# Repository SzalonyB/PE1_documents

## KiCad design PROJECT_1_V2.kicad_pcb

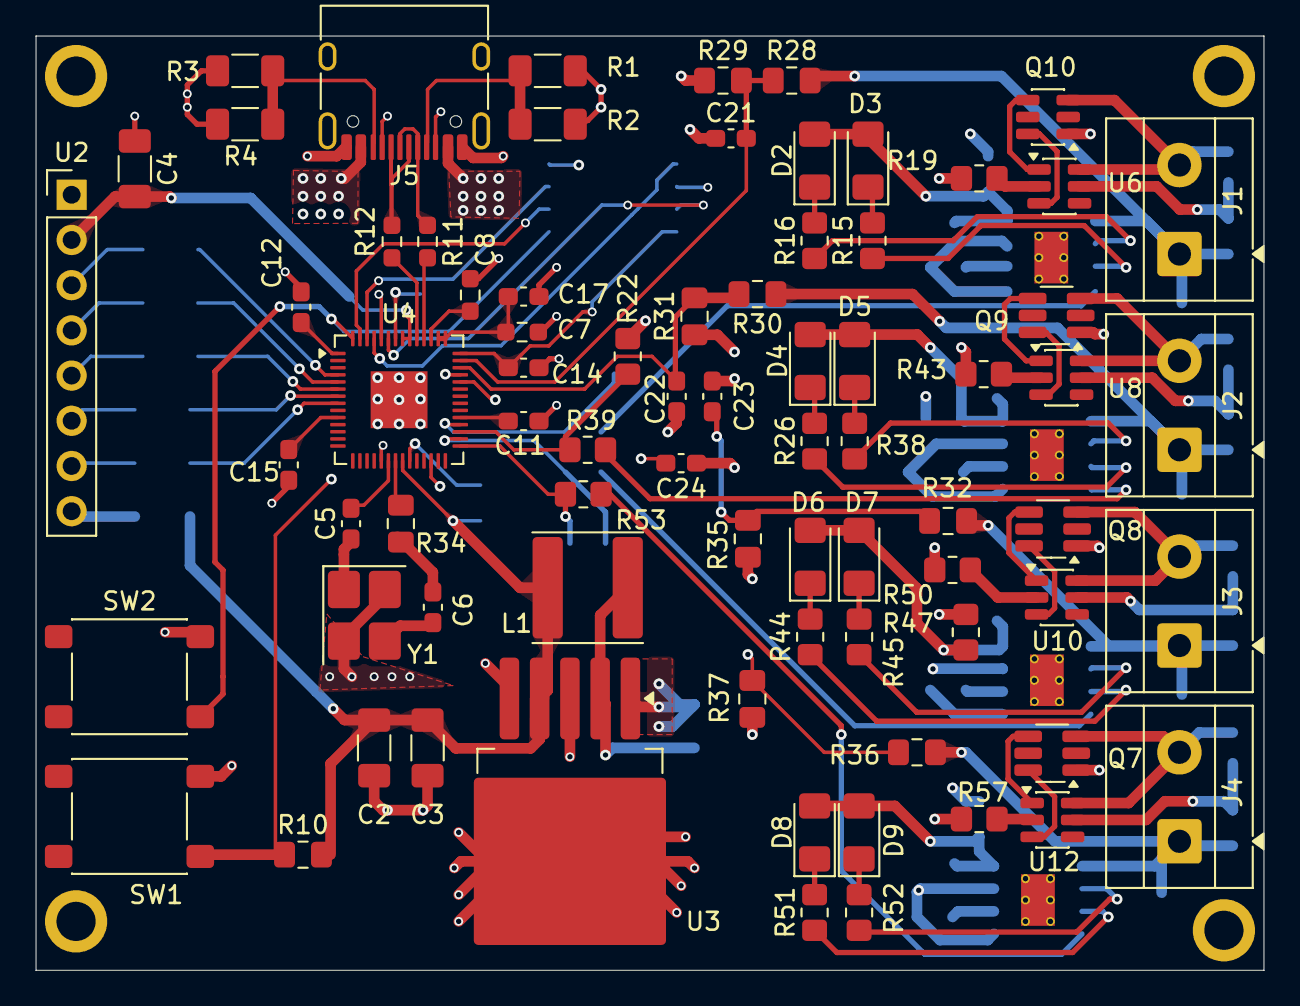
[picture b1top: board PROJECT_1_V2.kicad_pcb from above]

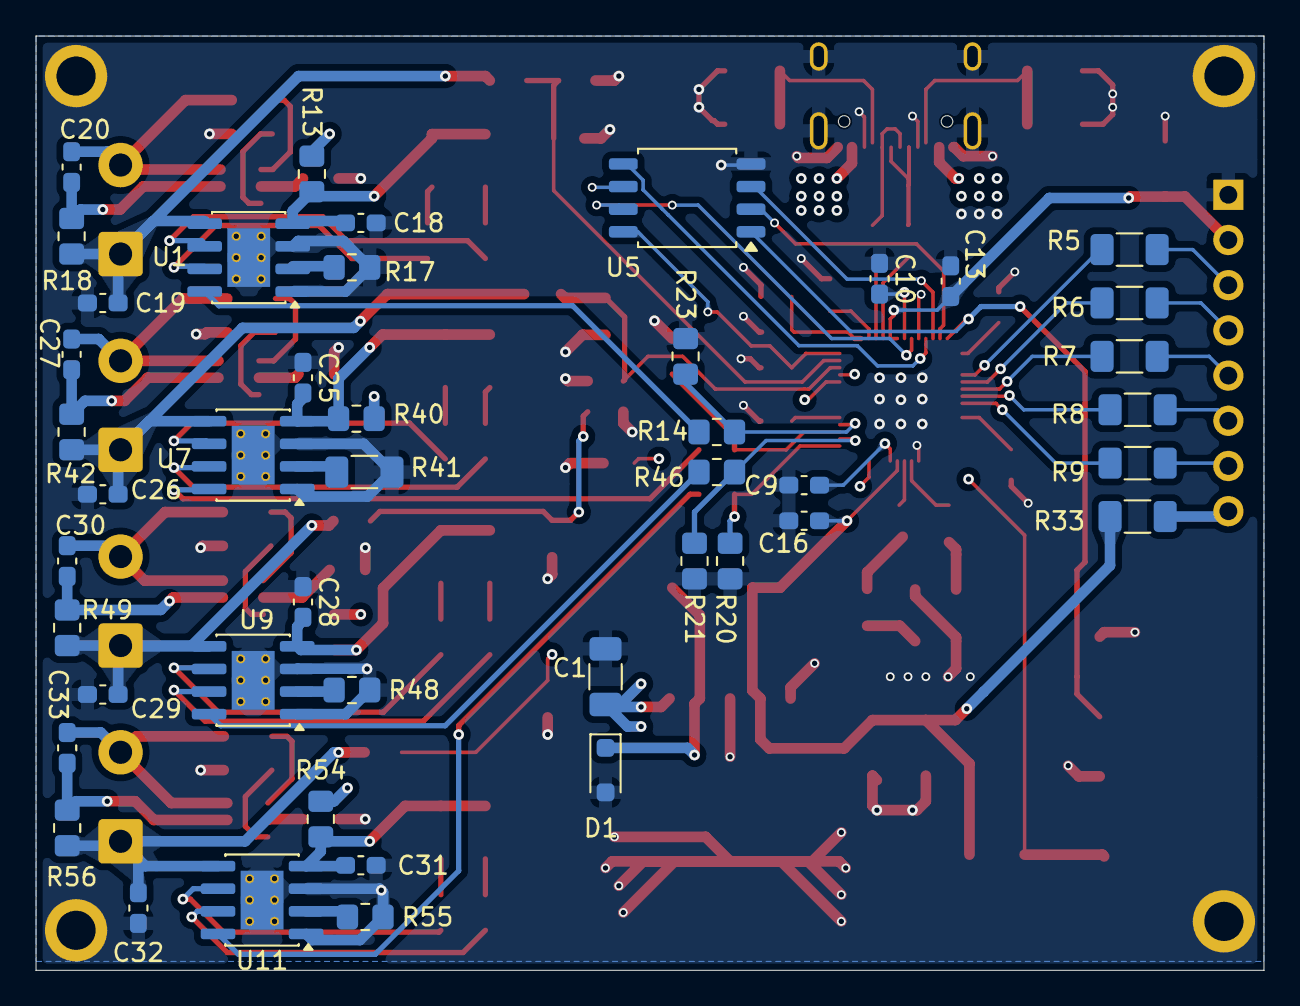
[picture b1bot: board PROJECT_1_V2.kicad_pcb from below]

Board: 4 copper layers, 69.0 x 52.5 mm, 125 parts (45 on the bottom side), 94 nets.

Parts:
C1, C2: 100uF; C_1206_3216Metric_Pad1.33x1.80mm_HandSolder
C3: 10nF; C_1206_3216Metric_Pad1.33x1.80mm_HandSolder
C4: 100nF; C_1206_3216Metric_Pad1.33x1.80mm_HandSolder
C5, C6: 15pF; C_0603_1608Metric_Pad1.08x0.95mm_HandSolder
C7: 1uf; R_0603_1608Metric_Pad0.98x0.95mm_HandSolder
C8: 1uF; R_0603_1608Metric_Pad0.98x0.95mm_HandSolder
C9, C10, C11, C12, C13, C14, C15, C16, C17, C20, C21, C22, C23, C24, C27, C30, C33: 100nF; C_0603_1608Metric_Pad1.08x0.95mm_HandSolder
C18, C19, C25, C26, C28, C29, C31, C32: 10uF; C_0603_1608Metric_Pad1.08x0.95mm_HandSolder
D1: 1N5892WS; D_SOD-323_HandSoldering
D2, D5, D7, D9: R LED; LED_1206_3216Metric_Pad1.42x1.75mm_HandSolder
D3, D4, D6, D8: G LED; LED_1206_3216Metric_Pad1.42x1.75mm_HandSolder
H1, H2, H3, H4: MountingHole_Pad; MountingHole_2.2mm_M2_ISO7380_Pad
J1, J2, J3, J4: Battery Input; TerminalBlock_MetzConnect_Type055_RT01502HDWU_1x02_P5.00mm_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
J5: USB_C_Receptacle_USB2.0_16P; USB_C_Receptacle_HRO_TYPE-C-31-M-12
L1: 100uH; L_APV_ANR6045
Q7, Q8, Q9: DMG9926UDM; SOT-23-6_Handsoldering
Q10: DMG9926UDM; SOT-23-6
R1, R2, R3, R4, R5, R6, R7, R9: 10k; R_1206_3216Metric_Pad1.30x1.75mm_HandSolder
R8: 1K; R_1206_3216Metric_Pad1.30x1.75mm_HandSolder
R10: 10K; C_0805_2012Metric_Pad1.18x1.45mm_HandSolder
R11, R12: 27; R_0603_1608Metric_Pad0.98x0.95mm_HandSolder
R13, R40, R47, R54: 0.5; R_0805_2012Metric_Pad1.20x1.40mm_HandSolder
R14, R15, R16, R26, R38, R39, R44, R45, R46, R51, R52, R53: 1k; R_0805_2012Metric_Pad1.20x1.40mm_HandSolder
R17, R48, R55: 1.2k; R_0805_2012Metric_Pad1.20x1.40mm_HandSolder
R18, R42, R49, R56: 100; R_0805_2012Metric_Pad1.20x1.40mm_HandSolder
R19, R43, R50, R57: 2k; R_0805_2012Metric_Pad1.20x1.40mm_HandSolder
R20, R21, R22, R23: 100k; R_0805_2012Metric_Pad1.20x1.40mm_HandSolder
R28, R30, R32, R36: 10k; C_0805_2012Metric_Pad1.18x1.45mm_HandSolder
R29, R31, R35, R37: 20k; C_0805_2012Metric_Pad1.18x1.45mm_HandSolder
R33: 220; R_1206_3216Metric_Pad1.30x1.75mm_HandSolder
R34: 1K; C_0805_2012Metric_Pad1.18x1.45mm_HandSolder
R41: 1.2k; R_1206_3216Metric_Pad1.30x1.75mm_HandSolder
SW1: RESET; SW_SPST_PTS645Sx43SMTR92
SW2: BOOT_LOADER; SW_SPST_PTS645Sx43SMTR92
U1, U7, U9: TP4056; SOIC-8-1EP_3.9x4.9mm_P1.27mm_EP2.41x3.3mm_ThermalVias
U2: Nokia_5110_LCD; PinHeader_1x08_P2.54mm_Vertical
U3: LM2576T-3.3; TO-263-5_TabPin3
U4: RP2040; QFN-56-1EP_7x7mm_P0.4mm_EP3.2x3.2mm
U5: W25Q128JVS; SOIC-8_5.3x5.3mm_P1.27mm
U6, U8, U10, U12: DW01A; SOT-23-6
U11: TP4056-42-ESOP8; SOIC-8-1EP_3.9x4.9mm_P1.27mm_EP2.41x3.3mm_ThermalVias
Y1: Crystal; Crystal_SMD_3225-4Pin_3.2x2.5mm_HandSoldering

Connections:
+1V1: C8.2, C9.2, C10.2, U4.23 (DVDD), U4.45 (VREG_VOUT), U4.50 (DVDD)
+3.3V: C2.2, C3.2, C4.2, C7.2, C11.2, C12.2, C13.2, C14.2, C15.2, C16.2, C17.2, L1.2, R10.2, R33.1, U2.2 (VCC), U3.4 (FB), U4.1 (IOVDD), U4.10 (IOVDD), U4.22 (IOVDD), U4.33 (IOVDD), U4.42 (IOVDD), U4.43 (ADC_AVDD), U4.44 (VREG_VIN), U4.48 (USB_VDD), U4.49 (IOVDD), U5.8 (VCC)
+5V: C1.2, J5.A4 (VBUS), J5.A9 (VBUS), J5.B4 (VBUS), J5.B9 (VBUS), R13.2, R40.2, R47.2, R54.2, U3.1 (VIN)
BAT+_1: C19.2, J1.1, R18.2, R28.2, U1.5 (BAT)
BAT+_2: C26.2, J2.1, R30.1, R42.2, U7.5 (BAT)
BAT+_3: C29.2, J3.1, R32.1, R49.2, U9.5 (BAT)
BAT+_4: C32.2, J4.1, R36.1, R56.2, U11.5 (BAT)
BOOT: SW2.1, U4.56 (~QSPI_SS), U5.1 (~CS)
CLK: R5.1, U4.4 (GPIO2)
CS: R8.1, U4.7 (GPIO5)
D+: J5.A6 (D+), J5.B6 (D+), R12.1
D-: J5.A7 (D-), J5.B7 (D-), R11.1
DIN: R6.1, U4.5 (GPIO3)
D/C: R7.1, U4.6 (GPIO4)
GATE_1: R14.1, R23.2, U4.32 (GPIO21)
GATE_2: R22.2, R39.1, U4.31 (GPIO20)
GATE_3: R21.2, R46.1, U4.30 (GPIO19)
GATE_4: R20.2, R53.1, U4.29 (GPIO18)
GND: C1.1, C2.1, C3.1, C4.1, C7.1, C8.1, C9.1, C10.1, C11.1, C12.1, C13.1, C14.1, C15.1, C16.1, C17.1, C18.1, C19.1, C21.1, C22.1, C23.1, C24.1, C25.1, C26.1, C28.1, C29.1, C31.1, C32.1, D1.2 (A), H1.1 (1_1), H2.1 (1_1), H3.1 (1_1), H4.1 (1_1), J5.A1 (GND), J5.A8 (SBU1), J5.A12 (GND), J5.B1 (GND), J5.B8 (SBU2), J5.B12 (GND), J5.SH, Q7.1 (S1), Q8.1 (D1), Q9.1 (D1), Q10.1 (D1), R1.2, R2.2, R3.2, R4.2, R17.2, R19.2, R20.1, R21.1, R22.1, R23.1, R29.1, R31.1, R35.1, R37.1, R41.2, R43.2, R48.2, R50.2, R55.2, R57.2, SW1.2 (A), SW2.2 (A), U1.1 (TEMP), U1.3 (GND), U1.9 (EPAD), U2.1 (GND), U3.3 (GND), U3.5 (~ON/OFF), U4.19 (TESTEN), U4.57 (GND), U5.4 (GND), U7.1 (TEMP), U7.3 (GND), U7.9 (EPAD), U9.1 (TEMP), U9.3 (GND), U9.9 (EPAD), U11.1 (TEMP), U11.3 (GND), U11.9 (EPAD), Y1.2, Y1.4
unnamed: C5.1, Y1.1
unnamed: C6.1, Y1.3
unnamed: C6.2, R34.2
unnamed: D1.1 (K), L1.1, U3.2 (OUT)
unnamed: C18.2, D2.2 (A), D3.2 (A), R13.1, U1.4 (V_{CC})
unnamed: D2.1 (K), R16.2
unnamed: D3.1 (K), R15.2
unnamed: C25.2, D4.2 (A), D5.2 (A), R40.1, U7.4 (V_{CC})
unnamed: D4.1 (K), R26.2
unnamed: D5.1 (K), R38.2
unnamed: C28.2, D6.2 (A), D7.2 (A), R47.1, U9.4 (V_{CC})
unnamed: D6.1 (K), R44.2
unnamed: D7.1 (K), R45.2
unnamed: C31.2, D8.2 (A), D9.2 (A), R54.1, U11.4 (V_{CC})
unnamed: D8.1 (K), R51.2
unnamed: D9.1 (K), R52.2
unnamed: C20.1, J1.2, Q10.3 (S2), U6.6 (GND)
unnamed: C27.1, J2.2, Q9.3 (S2), U8.6 (GND)
unnamed: C30.1, J3.2, Q8.3 (S2), U10.6 (GND)
unnamed: C33.1, J4.2, Q7.3 (S2), U12.6 (GND)
unnamed: J5.A5 (CC1), R1.1, R2.1
unnamed: J5.B5 (CC2), R3.1, R4.1
unnamed: Q7.6 (G1), U12.3 (OC)
unnamed: Q7.4 (G2), U12.1 (OD)
unnamed: Q8.6 (G1), U10.3 (OC)
unnamed: Q8.4 (G2), U10.1 (OD)
unnamed: Q9.6 (G1), U8.3 (OC)
unnamed: Q9.4 (G2), U8.1 (OD)
unnamed: Q10.6 (G1), U6.3 (OC)
unnamed: Q10.4 (G2), U6.1 (OD)
unnamed: R14.2, U1.8 (CE)
unnamed: R17.1, U1.2 (PROG)
unnamed: R15.1, U1.7 (~CHRG)
unnamed: R16.1, U1.6 (~STDBY)
unnamed: R5.2, U2.3 (CLK)
unnamed: R8.2, U2.6 (CS)
unnamed: R6.2, U2.4 (DIN)
unnamed: R7.2, U2.5 (D/~C)
unnamed: R33.2, U2.8 (LED)
unnamed: R9.2, U2.7 (~RST)
unnamed: R11.2, U4.46 (USB_DM)
unnamed: R12.2, U4.47 (USB_DP)
unnamed: R19.1, U6.2 (CS)
unnamed: C20.2, R18.1, U6.5 (VCC)
unnamed: R39.2, U7.8 (CE)
unnamed: R41.1, U7.2 (PROG)
unnamed: R26.1, U7.7 (~CHRG)
unnamed: R38.1, U7.6 (~STDBY)
unnamed: R43.1, U8.2 (CS)
unnamed: C27.2, R42.1, U8.5 (VCC)
unnamed: R46.2, U9.8 (CE)
unnamed: R48.1, U9.2 (PROG)
unnamed: R44.1, U9.7 (~CHRG)
unnamed: R45.1, U9.6 (~STDBY)
unnamed: R50.1, U10.2 (CS)
unnamed: C30.2, R49.1, U10.5 (VCC)
unnamed: R53.2, U11.8 (CE)
unnamed: R55.1, U11.2 (PROG)
unnamed: R51.1, U11.7 (~CHRG)
unnamed: R52.1, U11.6 (~STDBY)
unnamed: R57.1, U12.2 (CS)
unnamed: C33.2, R56.1, U12.5 (VCC)
QSPI_SCLK: U4.52 (QSPI_SCLK), U5.6 (CLK)
QSPI_SD0: U4.53 (QSPI_SD0), U5.5 (DI/IO_{0})
QSPI_SD1: U4.55 (QSPI_SD1), U5.2 (DO/IO_{1})
QSPI_SD2: U4.54 (QSPI_SD2), U5.3 (~WP/IO_{2})
QSPI_SD3: U4.51 (QSPI_SD3), U5.7 (~HOLD/~RESET/IO_{3})
RST: R9.1, U4.8 (GPIO6)
RUN: R10.1, SW1.1, U4.26 (RUN)
V_Sense1: C21.2, R28.1, R29.2, U4.41 (GPIO29/ADC3)
V_Sense2: C22.2, R30.2, R31.2, U4.40 (GPIO28/ADC2)
V_Sense3: C23.2, R32.2, R35.2, U4.39 (GPIO27/ADC1)
V_Sense4: C24.2, R36.2, R37.2, U4.38 (GPIO26/ADC0)
XIN: C5.2, U4.20 (XIN)
XOUT: R34.1, U4.21 (XOUT)

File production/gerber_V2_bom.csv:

Designator,Footprint,Quantity,Value,LCSC Part #
"C1, C2",1206,2,100uF,
"C10, C11, C12, C13, C14, C15, C16, C17, C20, C21, C22, C23, C24, C27, C30, C33, C9",0603,17,100nF,
"C18, C19, C25, C26, C28, C29, C31, C32",0603,8,10uF,
C3,1206,1,10nF,
C4,1206,1,100nF,
"C5, C6",0603,2,15pF,
"C7, C8",0603,2,1uf,
D1,D_SOD-323_HandSoldering,1,1N5892WS,
"D2, D5, D7, D9",1206,4,R LED,
"D3, D4, D6, D8",1206,4,G LED,
"J1, J2, J3, J4",TerminalBlock_MetzConnect_Type055_RT01502HDWU_1x02_P5.00mm_Horizontal,4,Battery Input,
J5,USB_C_Receptacle_HRO_TYPE-C-31-M-12,1,USB_C_Receptacle_USB2.0_16P,
L1,L_APV_ANR6045,1,100uH,
Q10,SOT-23-6,1,DMG9926UDM,
"Q7, Q8, Q9",SOT-23-6_Handsoldering,3,DMG9926UDM,
"R1, R2, R3, R4, R5, R6, R7, R9",1206,8,10k,
"R10, R28, R30, R32, R36",0805,5,10K,
"R11, R12",0603,2,27,
"R13, R40, R47, R54",0805,4,0.5,
"R14, R15, R16, R26, R34, R38, R39, R44, R45, R46, R51, R52, R53",0805,13,1k,
"R17, R48, R55",0805,3,1.2k,
"R18, R42, R49, R56",0805,4,100,
"R19, R43, R50, R57",0805,4,2k,
"R20, R21, R22, R23",0805,4,100k,
"R29, R31, R35, R37",0805,4,20k,
R33,1206,1,220,
R41,1206,1,1.2k,
R8,1206,1,1K,
SW1,SW_SPST_PTS645Sx43SMTR92,1,RESET,
SW2,SW_SPST_PTS645Sx43SMTR92,1,BOOT_LOADER,
"U1, U7, U9",SOIC-8-1EP_3.9x4.9mm_P1.27mm_EP2.41x3.3mm_ThermalVias,3,TP4056,
"U10, U12, U6, U8",SOT-23-6,4,DW01A,
U11,SOIC-8-1EP_3.9x4.9mm_P1.27mm_EP2.41x3.3mm_ThermalVias,1,TP4056-42-ESOP8,
U2,PinHeader_1x08_P2.54mm_Vertical,1,Nokia_5110_LCD,
U3,TO-263-5_TabPin3,1,LM2576T-3.3,
U4,QFN-56-1EP_7x7mm_P0.4mm_EP3.2x3.2mm,1,RP2040,
U5,SOIC-8_5.3x5.3mm_P1.27mm,1,W25Q128JVS,
Y1,Crystal_SMD_3225-4Pin_3.2x2.5mm_HandSoldering,1,Crystal,

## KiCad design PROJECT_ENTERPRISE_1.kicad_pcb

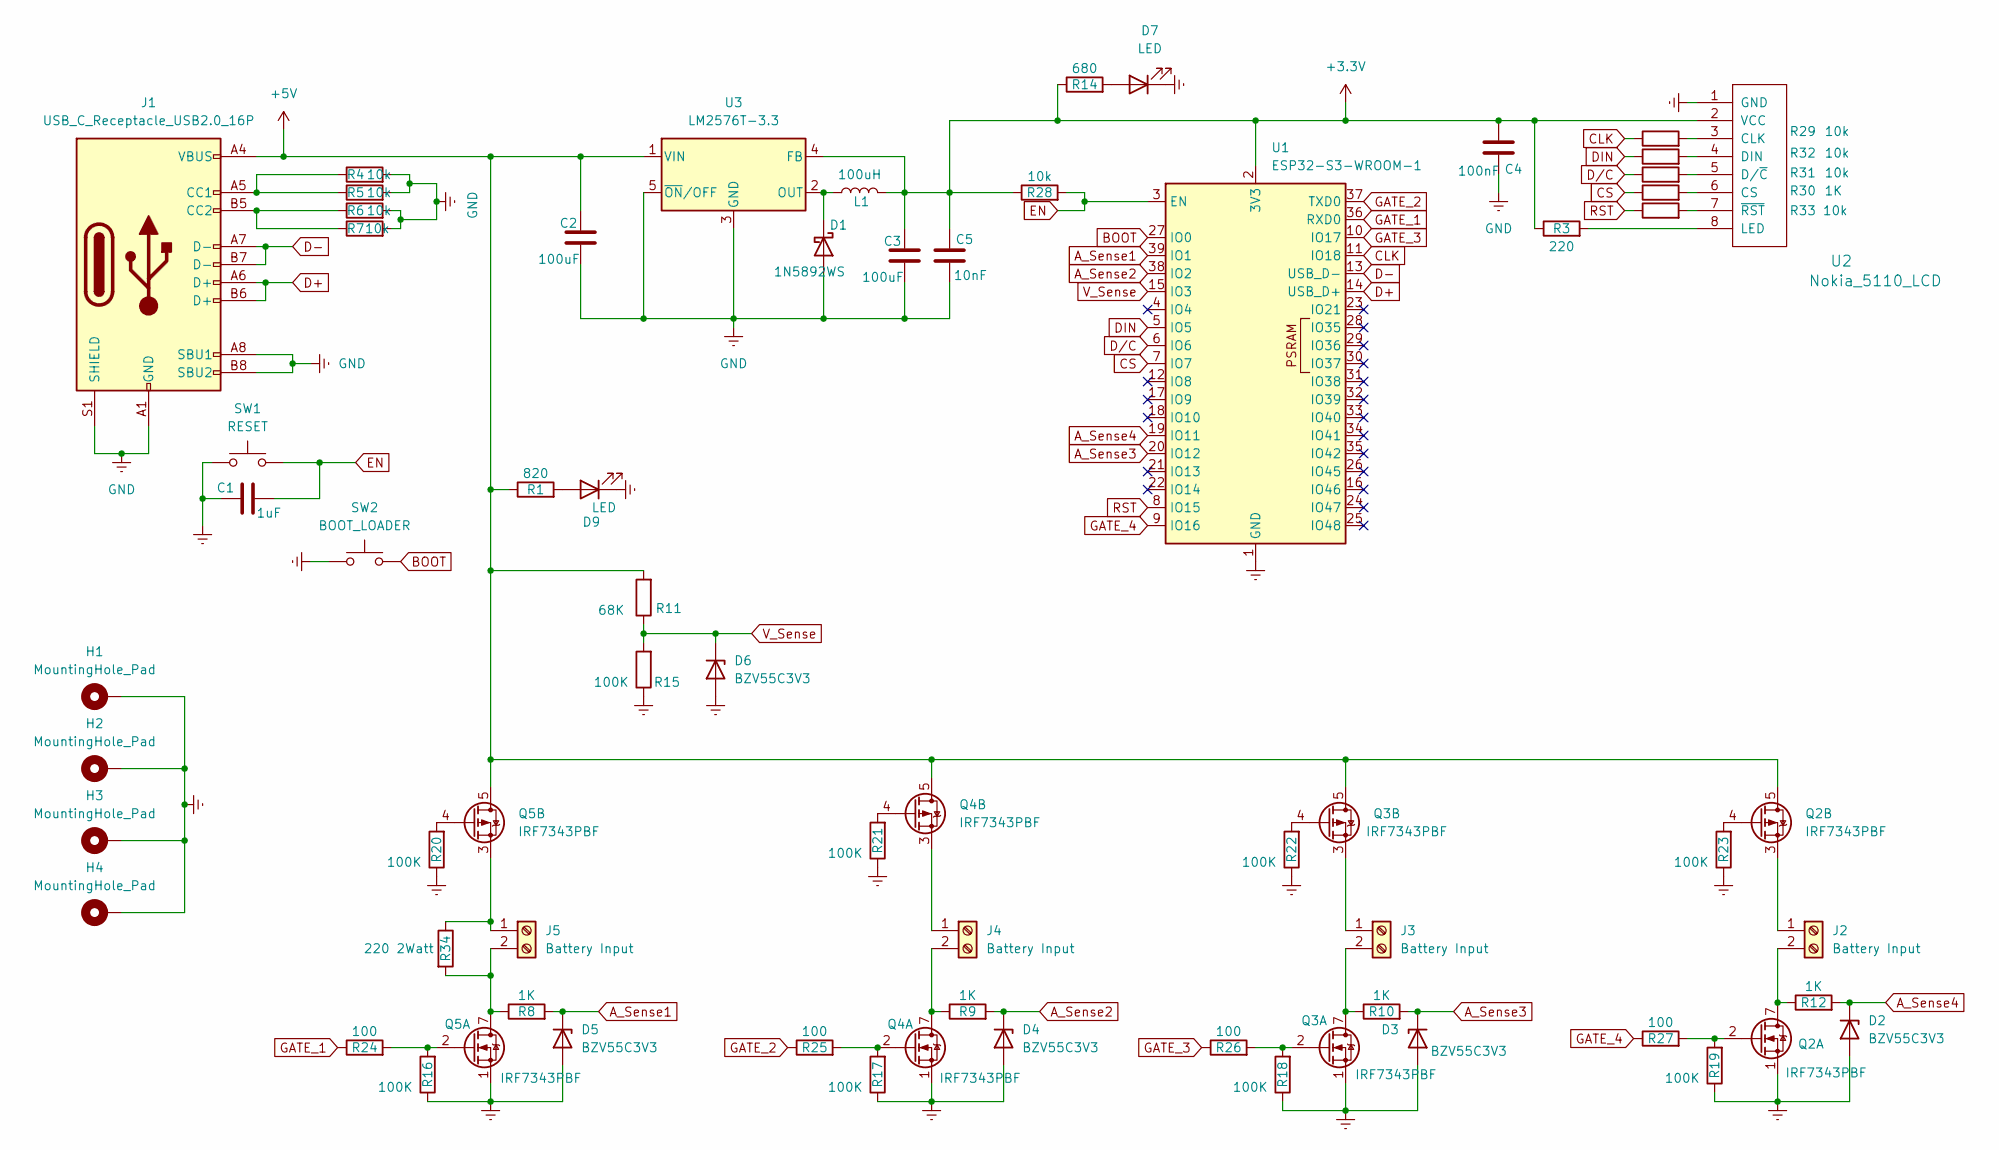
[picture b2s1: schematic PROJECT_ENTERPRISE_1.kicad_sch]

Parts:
C1: 1uF; C_1206_3216Metric_Pad1.33x1.80mm_HandSolder
C2, C3: 100uF; C_1206_3216Metric_Pad1.33x1.80mm_HandSolder
C4: 100nF; C_1206_3216Metric_Pad1.33x1.80mm_HandSolder
C5: 10nF; C_1206_3216Metric_Pad1.33x1.80mm_HandSolder
D1: 1N5892WS; D_SOD-323_HandSoldering
D2, D3, D4, D5, D6: BZV55C3V3; D_MiniMELF
D7, D9: LED; LED_1206_3216Metric_Pad1.42x1.75mm_HandSolder
H1, H2, H3, H4: MountingHole_Pad; MountingHole_2.2mm_M2_ISO7380_Pad
J1: USB_C_Receptacle_USB2.0_16P; USB_C_Receptacle_HRO_TYPE-C-31-M-12
J2, J3, J4, J5: Battery Input; TerminalBlock_MetzConnect_Type055_RT01502HDWU_1x02_P5.00mm_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
L1: 100uH; L_APV_ANR6045
Q2, Q3, Q4, Q5: IRF7343PBF; SOIC-8_3.9x4.9mm_P1.27mm
R1: 820; R_1206_3216Metric_Pad1.30x1.75mm_HandSolder
R3: 220; R_1206_3216Metric_Pad1.30x1.75mm_HandSolder
R4, R5, R6, R7, R28, R29, R31, R32, R33: 10k; R_1206_3216Metric_Pad1.30x1.75mm_HandSolder
R8, R9, R10, R12, R30: 1K; R_1206_3216Metric_Pad1.30x1.75mm_HandSolder
R11: 68K; R_1206_3216Metric_Pad1.30x1.75mm_HandSolder
R14: 680; R_1206_3216Metric_Pad1.30x1.75mm_HandSolder
R15, R16, R17, R18, R19, R20, R21, R22, R23: 100K; R_1206_3216Metric_Pad1.30x1.75mm_HandSolder
R24, R25, R26, R27: 100; R_1206_3216Metric_Pad1.30x1.75mm_HandSolder
R34: 220 2Watt; R_1206_3216Metric_Pad1.30x1.75mm_HandSolder
SW1: RESET; SW_SPST_PTS645Sx43SMTR92
SW2: BOOT_LOADER; SW_SPST_PTS645Sx43SMTR92
U1: ESP32-S3-WROOM-1
U2: Nokia_5110_LCD; PinHeader_1x08_P2.54mm_Vertical
U3: LM2576T-3.3; TO-263-5_TabPin3

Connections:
+3.3V: C3.2, C4.2, C5.2, L1.2, R3.1, R14.1, R28.1, U1.2 (3V3), U2.2 (VCC), U3.4 (FB)
+5V: C2.2, J1.A4 (VBUS), J1.A9 (VBUS), J1.B4 (VBUS), J1.B9 (VBUS), Q2.5 (D2), Q2.6 (D2), Q3.5 (D2), Q3.6 (D2), Q4.5 (D2), Q4.6 (D2), Q5.5 (D2), Q5.6 (D2), R1.1, R11.2, U3.1 (VIN)
A_Sense1: D5.1 (K), R8.2, U1.39 (IO1)
A_Sense2: D4.1 (K), R9.2, U1.38 (IO2)
A_Sense3: D3.1 (K), R10.2, U1.20 (IO12)
A_Sense4: D2.1 (K), R12.2, U1.19 (IO11)
BOOT: SW2.3 (B), SW2.4 (B), U1.27 (IO0); also elsewhere on the board
CLK: R29.1, U1.11 (IO18)
CS: R30.1, U1.7 (IO7)
D+: J1.A6 (D+), J1.B6 (D+), U1.14 (USB_D+)
D-: J1.A7 (D-), J1.B7 (D-), U1.13 (USB_D-)
DIN: R32.1, U1.5 (IO5)
D/C: R31.1, U1.6 (IO6)
EN: C1.1, R28.2, SW1.3 (B), SW1.4 (B), U1.3 (EN); also elsewhere on the board
GATE_1: R24.1, U1.36 (RXD0)
GATE_2: R25.1, U1.37 (TXD0)
GATE_3: R26.1, U1.10 (IO17)
GATE_4: R27.1, U1.9 (IO16)
GND: C1.2, C2.1, C3.1, C4.1, C5.1, D1.2 (A), D2.2 (A), D3.2 (A), D4.2 (A), D5.2 (A), D6.2 (A), D7.1 (K), D9.1 (K), H1.1 (1_1), H2.1 (1_1), H3.1 (1_1), H4.1 (1_1), J1.A1 (GND), J1.A8 (SBU1), J1.A12 (GND), J1.B1 (GND), J1.B8 (SBU2), J1.B12 (GND), J1.S1 (SHIELD), Q2.1 (S1), Q3.1 (S1), Q4.1 (S1), Q5.1 (S1), R4.2, R5.2, R6.2, R7.2, R15.1, R16.1, R17.1, R18.1, R19.1, R20.1, R21.1, R22.1, R23.1, SW1.1 (A), SW1.2 (A), SW2.1 (A), SW2.2 (A), U1.1 (GND), U1.40 (GND), U1.41 (GND), U2.1 (GND), U3.3 (GND), U3.5 (~ON/OFF); also elsewhere on the board
unnamed: D1.1 (K), L1.1, U3.2 (OUT)
unnamed: D7.2 (A), R14.2
unnamed: D9.2 (A), R1.2
unnamed: J1.A5 (CC1), R4.1, R5.1
unnamed: J1.B5 (CC2), R6.1, R7.1
unnamed: J2.1, Q2.3 (S2)
unnamed: J2.2, Q2.7 (D1), Q2.8 (D1), R12.1
unnamed: J3.1, Q3.3 (S2)
unnamed: J3.2, Q3.7 (D1), Q3.8 (D1), R10.1
unnamed: J4.1, Q4.3 (S2)
unnamed: J4.2, Q4.7 (D1), Q4.8 (D1), R9.1
unnamed: J5.1, Q5.3 (S2), R34.1
unnamed: J5.2, Q5.7 (D1), Q5.8 (D1), R8.1, R34.2
unnamed: Q2.2 (G1), R19.2, R27.2
unnamed: Q2.4 (G2), R23.2
unnamed: Q3.2 (G1), R18.2, R26.2
unnamed: Q3.4 (G2), R22.2
unnamed: Q4.2 (G1), R17.2, R25.2
unnamed: Q4.4 (G2), R21.2
unnamed: Q5.2 (G1), R16.2, R24.2
unnamed: Q5.4 (G2), R20.2
unnamed: R29.2, U2.3 (CLK)
unnamed: R30.2, U2.6 (CS)
unnamed: R32.2, U2.4 (DIN)
unnamed: R31.2, U2.5 (D/~C)
unnamed: R3.2, U2.8 (LED)
unnamed: R33.2, U2.7 (~RST)
RST: R33.1, U1.8 (IO15)
V_Sense: D6.1 (K), R11.1, R15.2, U1.15 (IO3)

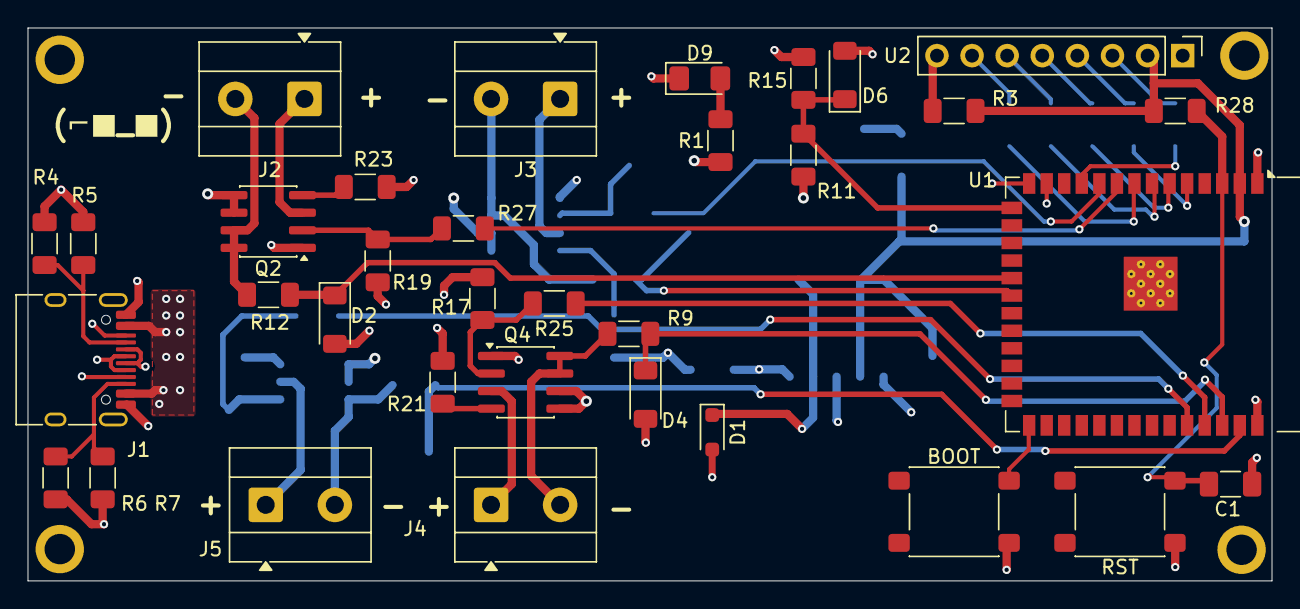
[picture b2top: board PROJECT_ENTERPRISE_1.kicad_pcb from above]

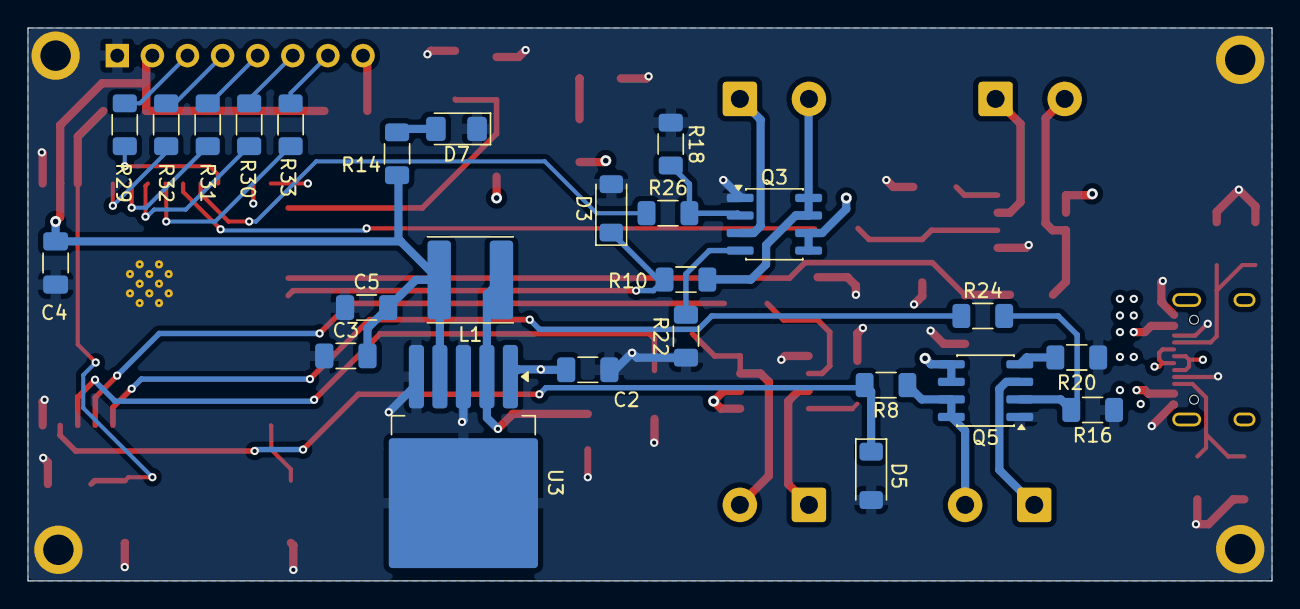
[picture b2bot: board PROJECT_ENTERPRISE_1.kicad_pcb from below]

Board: 4 copper layers, 90.0 x 40.0 mm, 63 parts (25 on the bottom side), 48 nets.

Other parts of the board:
BOOT: BOOT_LOADER; SW_SPST_PTS645Sx43SMTR92
RST: RST; SW_SPST_PTS645Sx43SMTR92

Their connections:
BOOT: BOOT.3 (B), BOOT.4 (B); also elsewhere on the board
EN: RST.1 (A), RST.2 (A); also elsewhere on the board
GND: BOOT.1 (A), BOOT.2 (A), RST.3 (B), RST.4 (B); also elsewhere on the board

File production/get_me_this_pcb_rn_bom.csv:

Designator,Footprint,Quantity,Value,LCSC Part #
BOOT,SW_SPST_PTS645Sx43SMTR92,1,BOOT_LOADER,
C1,1206,1,1uF,
"C2, C3",1206,2,100uF,
C4,1206,1,100nF,
C5,1206,1,10nF,
D1,D_SOD-323_HandSoldering,1,1N5892WS,
"D2, D3, D4, D5, D6",D_MiniMELF,5,BZV55C3V3,
"D7, D9",1206,2,LED,
J1,USB_C_Receptacle_HRO_TYPE-C-31-M-12,1,USB_C_Receptacle_USB2.0_16P,
"J2, J3, J4, J5",TerminalBlock_MetzConnect_Type055_RT01502HDWU_1x02_P5.00mm_Horizontal,4,Battery Input,
L1,L_APV_ANR6045,1,100uH,
"Q2, Q3, Q4, Q5",SOIC-8_3.9x4.9mm_P1.27mm,4,IRF7343PBF,
R1,1206,1,820,
"R10, R12, R30, R8, R9",1206,5,1K,
R11,1206,1,68K,
R14,1206,1,680,
"R15, R16, R17, R18, R19, R20, R21, R22, R23",1206,9,100K,
"R24, R25, R26, R27",1206,4,100,
"R28, R29, R31, R32, R33, R4, R5, R6, R7",1206,9,10k,
R3,1206,1,220,
RST,SW_SPST_PTS645Sx43SMTR92,1,RST,
U1,ESP32-S3-WROOM-1,1,ESP32-S3-WROOM-1,
U2,PinHeader_1x08_P2.54mm_Vertical,1,Nokia_5110_LCD,
U3,TO-263-5_TabPin3,1,LM2576T-3.3,

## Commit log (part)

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2026-05-22 Added datasheets.
2026-05-23 added the code
2026-05-23 Added the rest
2026-05-23 Final product.
2026-05-26 Added comments
2026-05-26 more comments
2026-06-19 transistor
